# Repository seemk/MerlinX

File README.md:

MerlinX
=======

Electronics overhaul for Merlin 6.

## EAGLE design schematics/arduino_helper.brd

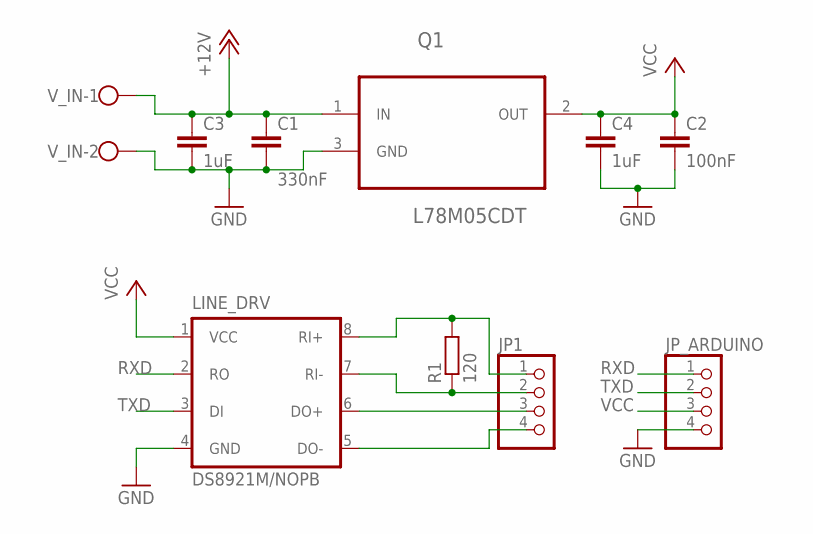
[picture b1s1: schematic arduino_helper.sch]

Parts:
C1: 330nF; C0805
C2: 100nF; C0805
C3, C4: 1uF; C0805
JP1: PINHD-1X4; 1X04
JP_ARDUINO: PINHD-1X4; 1X04
LINE_DRV: DS8921M/NOPB; SOIC8
Q1: L78M05CDT; TO225P972X240-3N
R1: 120; R0805
V_IN: W237-102

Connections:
+12V: C1.1, C3.1, Q1.1 (IN), V_IN.1
DO+: JP1.3, LINE_DRV.6 (DO+)
DO-: JP1.4, LINE_DRV.5 (DO-)
GND: C1.2, C2.2, C3.2, C4.2, JP_ARDUINO.4, LINE_DRV.4 (GND), Q1.3 (GND), V_IN.2
RI+: JP1.1, LINE_DRV.8 (RI+), R1.2
RI-: JP1.2, LINE_DRV.7 (RI-), R1.1
RXD: JP_ARDUINO.1, LINE_DRV.2 (RO)
TXD: JP_ARDUINO.2, LINE_DRV.3 (DI)
VCC: C2.1, C4.1, JP_ARDUINO.3, LINE_DRV.1 (VCC), Q1.2 (OUT)

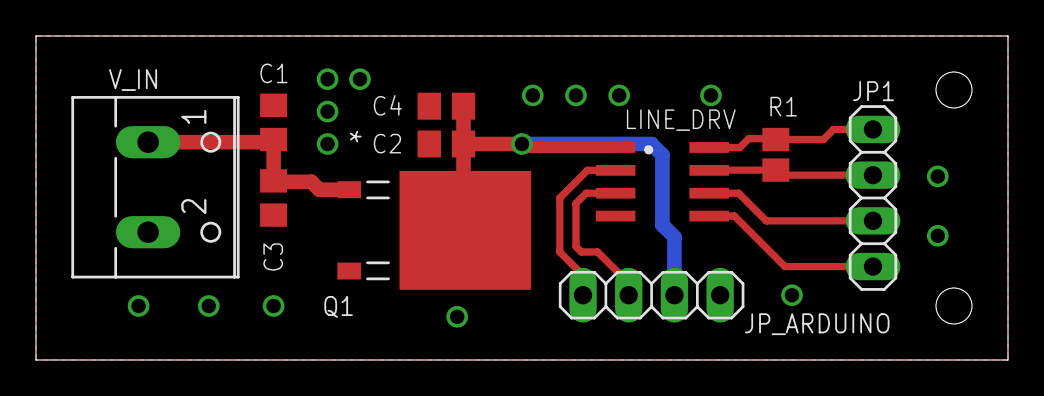
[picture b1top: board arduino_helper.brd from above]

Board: 2 copper layers, 54.0 x 18.0 mm, 10 parts (0 on the bottom side), 9 nets.

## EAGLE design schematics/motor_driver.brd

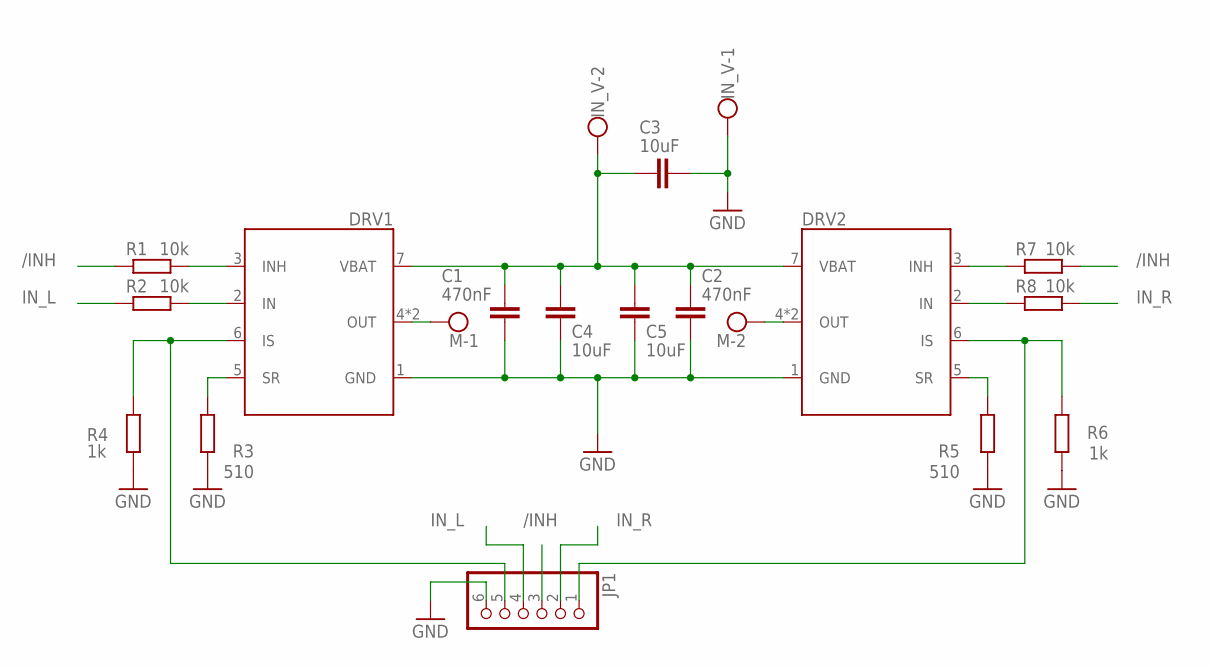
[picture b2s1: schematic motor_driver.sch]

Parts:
C1, C2: 470nF; C0805
C3, C4, C5: 10uF; C1206
DRV1, DRV2: FAN7093_F085SMD; TO-263-8
IN_V: W237-102
JP1: PINHD-1X6; 1X06
M: W237-102
R1, R2, R7, R8: 10k; R0805
R3, R5: 510; R0805
R4, R6: 1k; R0805

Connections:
/INH: JP1.3, R1.1, R7.2
GND: C1.2, C2.2, C3.2, C4.2, C5.2, DRV1.1 (GND), DRV2.1 (GND), IN_V.1, JP1.6, R3.1, R4.2, R5.1, R6.1
IN_L: JP1.4, R2.1
IN_R: JP1.2, R8.2
IS_L: DRV1.6 (IS), JP1.5, R4.1
IS_R: DRV2.6 (IS), JP1.1, R6.2
unnamed: DRV1.2 (IN), R2.2
unnamed: DRV1.3 (INH), R1.2
unnamed: DRV1.5 (SR), R3.2
unnamed: DRV1.4 (OUT), DRV1.8 (OUT), M.1
unnamed: DRV2.4 (OUT), DRV2.8 (OUT), M.2
unnamed: DRV2.5 (SR), R5.2
unnamed: DRV2.2 (IN), R8.1
unnamed: DRV2.3 (INH), R7.1
VSS: C1.1, C2.1, C3.1, C4.1, C5.1, DRV1.7 (VBAT), DRV2.7 (VBAT), IN_V.2

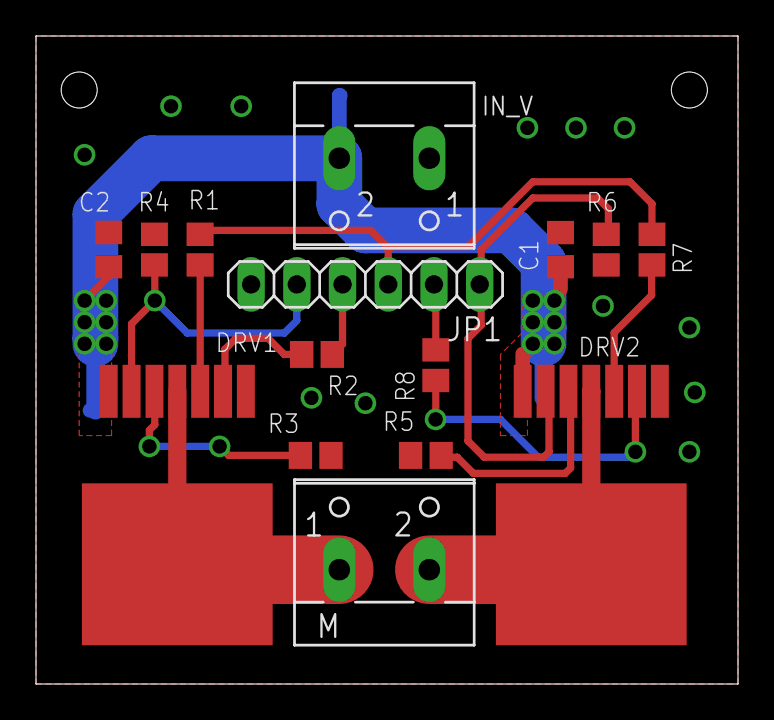
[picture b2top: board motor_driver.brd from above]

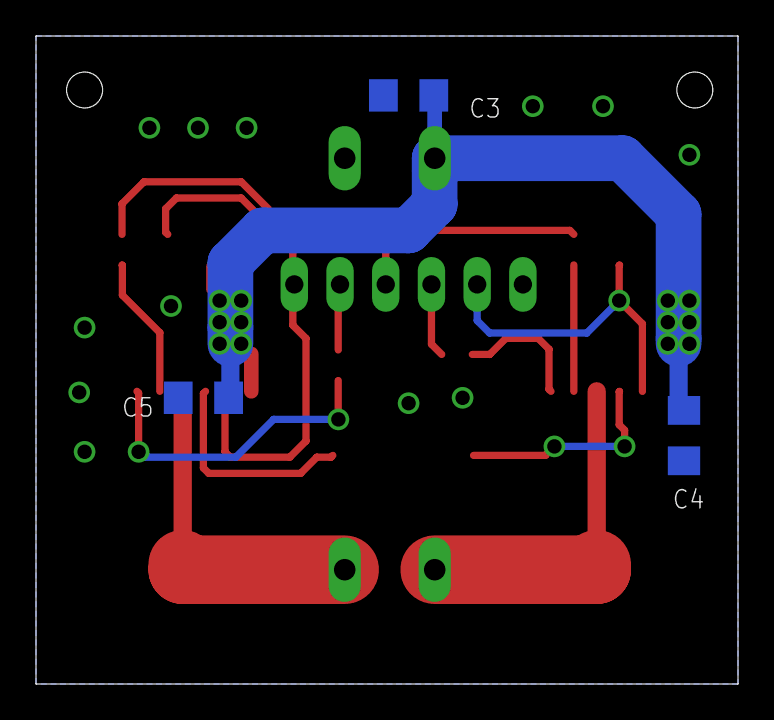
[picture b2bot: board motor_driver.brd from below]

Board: 2 copper layers, 39.0 x 36.0 mm, 18 parts (3 on the bottom side), 15 nets.

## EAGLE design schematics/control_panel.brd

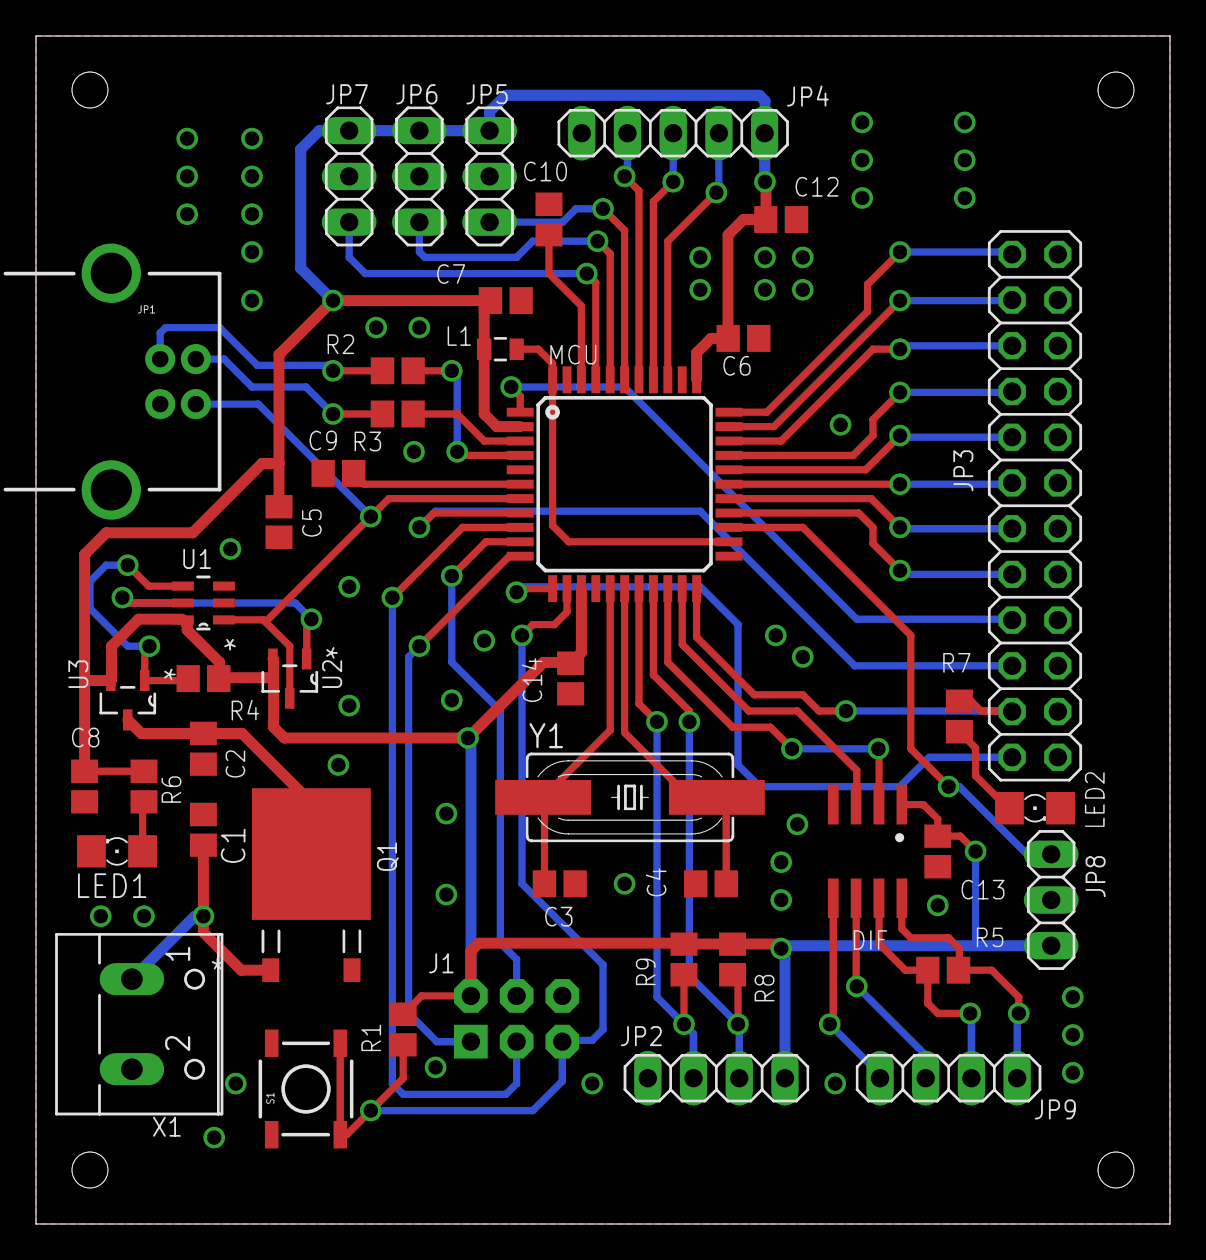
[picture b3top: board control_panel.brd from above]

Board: 2 copper layers, 63.0 x 66.0 mm, 44 parts (0 on the bottom side), 49 nets.

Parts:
C1: 330nF; C0805
C2, C5, C6, C7, C8, C9, C10, C12, C13, C14: 100nF; C0805
C3, C4: 22pF; C0805
DIF: DS8921M/NOPB; SOIC8
J1: AVR_SPI_PRG_6NS; 2X3-NS
JP1: USB-B; USB-B-PTH
JP2, JP9: 1X04
JP3: 2X12
JP4: 1X05
JP5, JP6, JP7, JP8: 1X03
L1: 10uH; 0805
LED1, LED2: FKIT-LED-1206
MCU: ATMEGA32U4TQFP; SPARKFUN-DIGITALIC_TQFP44
Q1: L78M05CDT; TO225P972X240-3N
R1, R8, R9: 10k; R0805
R2, R3: 22; R0805
R4: 470k; R0805
R5: 120; R0805
R6, R7: 330; R0805
S1: TACTILE_SWITCH_SMD
U1: LTC4412ES6TRMPBF; SOT95P280X100-6N
U2, U3: NX2301P; SOT95P230X110-3N
X1: W237-102
Y1: HC49UP

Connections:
BTN_1: JP3.16, MCU.29
BTN_2: JP3.14, MCU.28
BTN_3: JP3.8, MCU.1
BTN_4: JP3.12, MCU.27
BTN_5: JP3.20, MCU.31
BTN_6: JP3.24, MCU.33
BTN_7/LED: JP3.4, MCU.22, R7.2
BTN_CAM_CENTER: JP3.18, MCU.30
BTN_CAM_DOWN: JP3.22, MCU.32
BTN_CAM_LEFT: JP3.10, MCU.26
BTN_CAM_RIGHT: JP3.2, MCU.12
BTN_CAM_UP: JP3.6, MCU.8
D+: JP1.D+, R2.2
D-: JP1.D-, R3.2
DO+: DIF.6, JP9.3
DO-: DIF.5, JP9.4
GATE: U1.5, U2.1
GND: C1.2, C2.2, C3.1, C4.1, C5.2, C6.1, C7.1, C8.2, C9.1, C10.2, C12.2, C13.1, C14.1, DIF.4, J1.6, JP1.GND, JP2.1, JP3.1, JP3.3, JP3.5, JP3.7, JP3.9, JP3.11, JP3.13, JP3.15, JP3.17, JP3.19, JP3.21, JP3.23, JP4.1, JP5.2, JP6.2, JP7.2, JP8.2, LED1.C, LED2.C, MCU.5, MCU.15, MCU.23, MCU.35, MCU.43, Q1.3, S1.1, S1.2, U1.2, U1.3, X1.2
JS1: JP4.4, MCU.36
JS2: JP4.3, MCU.37
JS_REF: JP4.2, MCU.38
MISO: J1.1, MCU.11
MOSI: J1.4, MCU.10
unnamed: C3.2, MCU.16, Y1.1
unnamed: C4.2, MCU.17, Y1.2
unnamed: R4.2, U1.4, U3.1
unnamed: DIF.2, MCU.20
unnamed: C9.2, MCU.6
unnamed: MCU.4, R2.1
unnamed: MCU.3, R3.1
unnamed: LED1.A, R6.1
unnamed: LED2.A, R7.1
unnamed: DIF.3, MCU.21
unnamed: L1.2, MCU.24, MCU.44
unnamed: C10.1, MCU.42
POT1: JP5.1, MCU.39
POT2: JP6.1, MCU.40
POT3: JP7.1, MCU.41
POT4: JP8.1, MCU.25
RESET: J1.5, MCU.13, R1.1, S1.3, S1.4
RI+: DIF.8, JP9.1, R5.2
RI-: DIF.7, JP9.2, R5.1
SCK: J1.3, MCU.9
SCL: JP2.2, MCU.18, R9.1
SDA: JP2.3, MCU.19, R8.1
VBUS: JP1.VBUS, MCU.7, U1.1, U2.3
VCC: C5.1, C6.2, C7.2, C8.1, C12.1, C13.2, C14.2, DIF.1, J1.2, JP2.4, JP4.5, JP5.3, JP6.3, JP7.3, JP8.3, L1.1, MCU.2, MCU.14, MCU.34, R1.2, R4.1, R6.2, R8.2, R9.2, U1.6, U2.2, U3.2
V_EXT: C2.1, Q1.2, U3.3
V_IN: C1.1, Q1.1, X1.1

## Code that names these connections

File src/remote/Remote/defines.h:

#ifndef CONSTANTS_H_
#define CONSTANTS_H_

#define F_CPU 16000000UL
#define CPU_PRESCALE(n) (CLKPR = 0x80, CLKPR = (n))

// IO pins
#define LED PD5
#define BTN_CAM_UP PC7
#define BTN_CAM_DOWN PC6
#define BTN_CAM_CENTER PB6
#define BTN_CAM_LEFT PB5
#define BTN_CAM_RIGHT PB4
#define BTN_LIGHT PD7
// Unused pins, currently placeholders for extra buttons. Should still be set as inputs
#define BTN_HOVER_DECREASE PD6
#define BTN_HOVER_INCREASE PE6
#define BTN_UU3 PB0
#define BTN_UU4 PB7

#define output_low(port,pin) port &= ~(1<<pin)
#define output_high(port,pin) port |= (1<<pin)
#define set_input(portdir,pin) portdir &= ~(1<<pin)
#define set_output(portdir,pin) portdir |= (1<<pin)

#define BTN_PRESSED(pin, btn) (!(pin & (1 << btn)))
#define cmd_begin 0x7e
#define cmd_end   0x7f

#endif

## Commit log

2013-10-27 Added schematics, gitignore.
2013-10-29 Added arduino helper board.
2013-10-30 Widened supply wires on the driver, changed wire positions on control panel board.
2013-11-05 Added a common ground for the driver.
2013-11-06 Extra caps, wider supply traces for the Arduino helper PCB.
2013-11-06 Widened supply traces.
2013-11-06 Added extra supply caps.
2013-11-06 Added extra GND vias.
2013-12-05 Initial project skeleton for remote controller
2013-12-12 Added USB and serial console.
2013-12-12 Joystick position reading, additional console debugging.
2014-01-02 Added joystick position mapping.
2014-01-02 Updated gitignore.
2014-01-05 Added names to unnamed signals.
2014-01-19 Added console button debug print.
2014-01-26 Camera pad controlling.
2014-01-27 Added motor controls, hover ADC.
2014-01-27 Hover motoring, yay
2014-11-04 Some cleanup, moving remote to arduino
2014-11-24 Added digital button reads.

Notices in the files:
parts and their libraries:
SparkFun-FreqCtrl: Licensing: CC v3.0 Share-Alike You are welcome to use this library for commercial purposes.
